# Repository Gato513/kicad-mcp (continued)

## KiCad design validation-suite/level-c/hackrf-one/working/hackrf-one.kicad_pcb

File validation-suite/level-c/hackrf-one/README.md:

# HackRF One (Great Scott Gadgets) — Validation Suite, Nivel C-01

Primera y ancla del Nivel C (complejidad alta / frontera refutatoria) del
flujo canónico de `kicad-mcp` (sesión 33, Fase 4, D-30.1/D-30.4). Tercer y
último punto de evidencia sobre los umbrales D-30.3 — cierra la trilogía
A ([anavi-dev-mic](../../level-a/anavi-dev-mic/)) + B
([anavi-macro-pad-12](../../level-b/anavi-macro-pad-12/)) + C. Hereda el
template metodológico establecido por Nivel A/B.

## Origen

- **Upstream**: https://github.com/greatscottgadgets/hackrf
  (`hardware/hackrf-one/`).
- **Commit canónico**: `24b53345afb79ebe34129bb68396614ab75f5637`
  ("HackRF One: update version to 10"), branch `main`.
- **Licencia**: **CERN-OHL-P v2** (permisiva) — verificado localmente
  contra el archivo `LICENSE` del propio directorio. **Corrige una
  premisa del prompt de sesión**, que citaba GPL-2/CC-BY (esa combinación
  aplica al firmware/software del proyecto HackRF más amplio, no al
  hardware de `hackrf-one/`, que tiene su propio `LICENSE`).
- **Descripción**: SDR (software-defined radio) de 1 MHz a 6 GHz, USB 2.0,
  MCU + CPLD + frontend RF, 4 capas.

## Admisión (6 criterios, D-33.1 — cada uno con su refutación explícita)

1. **PCB fabricada**: ✅ producto comercial en venta activa por Great Scott
   Gadgets (referencia industrial, featured en KiCad.org "Made with
   KiCad"). Refutación buscada: ¿evidencia más allá del propio repo? Sí —
   es hardware ampliamente distribuido y clonado (7.9k★/1.7k forks),
   citado en publicaciones de seguridad/RF.
2. **Proyecto mantenido**: ⚠️ **matiz, no refutación limpia**. Verificado
   localmente (`git log -- hardware/hackrf-one/`): último commit
   **2023-12-11** (`24b53345`, "update version to 10"), no 2024-02-07 como
   había estimado una verificación remota previa (LLM) — **corrección
   D-33.1**: la fecha remota inicial era incorrecta, la real es aún más
   vieja (~2 años 8 meses al momento de sesión 33). Dispara el trigger de
   ">2 años sin commits sobre hardware" del prompt. **Decisión del
   arquitecto (`AskUserQuestion`, pre-Bloque 0): admitir de todas formas**
   — producto en venta activa, hardware r10 estable, sin necesidad de
   revisión de layout desde entonces. Existe rama `h1r9` (revisión r9) no
   evaluada — fuera de alcance, `main` es la referencia.
3. **Buenas prácticas de KiCad**: ✅ revisión OK — stackup RF documentado
   explícitamente en el `.kicad_pcb` (dieléctricos con espesor real),
   netclasses declaradas (`Default` únicamente — ver "Hallazgo
   estructural" abajo), símbolo custom (`74AUP2G58GU.kicad_sym`) con
   `sym-lib-table`/`fp-lib-table` propios.
4. **Licencia compatible**: ✅ CERN-OHL-P v2 (permisiva) — mejor que lo
   estimado en el prompt.
5. **Esquemático + PCB completos**: ✅, con matiz — **`.kicad_sch` es
   MULTI-HOJA** (`grep -c "(sheet " hackrf-one.kicad_sch` = 3: `baseband`,
   `frontend`, `mcu`). Primera entrada jerárquica de la Suite. **No
   bloquea**: verificado que ni `run_erc()` ni
   `get_world_context(kind="sch")` se usan en el flujo canónico de Nivel
   A/B (grep sobre ambos `validation-report.md`, cero hits) — el flujo va
   por `route_board`/`fill_zones`/etc. contra el **board vivo**
   (`kind="pcb"`), que no tiene noción de jerarquía de esquemático.
6. **DRC 0/0 en el ground truth**: ❌ **NO cumple** — 470 violaciones
   totales en el original (22 `error`, 448 `warning` según el campo
   `severity` del JSON de `kicad-cli`; 0 `unconnected_items`). **Mismo
   precedente sancionado
   que Nivel A/B** (excepción documentada): el desglose (`text_height`
   ×199, `lib_footprint_mismatch` ×199, `lib_footprint_issues` ×23,
   `starved_thermal` ×13, `text_thickness` ×13, `silk_edge_clearance`
   ×13, `footprint_type_mismatch` ×7, `padstack` ×2,
   `nonmirrored_text_on_back_layer` ×1) es mayoritariamente cosmético o
   producto de no tener localmente las librerías custom exactas del
   autor (`lib_footprint_mismatch`/`lib_footprint_issues`, 222/470 = 47%)
   — mismo patrón ya visto en ambos niveles previos. **0 `unconnected_items`
   confirma que el ground truth está 100% ruteado** (no hay indicio de
   que el autor haya dejado nets sin conectar).

## Diversidad D-30.4 (features nuevas de Nivel C)

Contra `validation-suite/reports/coverage-matrix.md` (estado post Nivel B):

- **4 capas de cobre reales** (`F.Cu`≡`C1F`, `In1.Cu`≡`C2`, `In2.Cu`≡`C3`,
  `B.Cu`≡`C4B` — nombres de capa custom del autor, no los canónicos de
  KiCad) — primera entrada de la Suite. **Nota importante para Bloque
  2/3**: en el ground truth, las capas internas concentran la MAYORÍA del
  cobre (`C2` 8182mm², `C3` 7767mm² — más que `C1F`/`C4B` juntas) pero
  casi ningún track de señal (`C2` 29 segmentos, `C3` 15 segmentos, vs.
  `C1F` 2848 y `C4B` 925) — el ground truth mismo usa las capas internas
  casi exclusivamente como **planos**, no para rutear señal. Esto
  recalibra la expectativa de H1b: "0 tracks de señal en capas internas"
  en el output NO sería necesariamente una refutación si el ground truth
  tampoco los tiene.
- **Stackup RF real** con espesores de dieléctrico declarados (prepreg
  0.2104mm ×2, core 1.065mm — total 1.6116mm) — primera vez que la Suite
  ejercita un `.kicad_pcb` con `(stackup ...)` no trivial.
- **Escala**: 437 footprints / 380 nets / 3817 segmentos / 498 vías — ~8×
  Nivel B en nets (48), ~7× en footprints (63). Salto de escala, no
  incremental.
- **Esquemático jerárquico multi-hoja** (3 sub-hojas) — primera vez.
- **Footprints QFN/alta densidad** — MCU (LPC4320) y CPLD en QFN,
  densidad global del ground truth 90.17% (capa `C2`, la de mayor
  cobre) — más denso que Nivel B (63.88% B.Cu).
- **RF**: conectores SMA, antena, frontend de RF con componentes pasivos
  de precisión — régimen no ejercitado por A/B.
- **USB 2.0** (conector propio en el board, a diferencia de A/B donde el
  USB vivía dentro de un módulo XIAO externo) — primera vez con cobre de
  USB propio en la Suite.

**No confirmado como diversidad — refutado antes de ejecutar (D-33.1)**:
netclasses de impedancia. Ver "Hallazgo estructural" abajo.

## Hallazgo estructural (refutación D-33.1, previa a cualquier ejecución)

Verificado localmente contra `hackrf-one.kicad_pro` (`net_settings.classes`):
el ground truth define **una única netclass `Default`**
(track 0.127mm, clearance 0.127mm, vía 0.4572/0.254mm, con
`diff_pair_width`/`diff_pair_gap` poblados pero **sin ninguna asignación
de net** a clases distintas de `Default`). Mismo patrón que **todos** los
proyectos ANAVI verificados en Nivel A/B (BACKLOG P2, "ningún proyecto del
catálogo ANAVI asigna netclasses en la práctica").

⇒ **La sub-hipótesis de H1b "netclasses respetadas" queda refutada por el
propio ground truth, antes de tocar `route_board`.** No es un hallazgo
nuevo sobre el código (ya documentado en BACKLOG P2 desde sesión 32,
"candidato a Nivel C/D si aparece un board con asignación real") — HackRF
One tampoco la ejercita. El control de impedancia de este board es
**geométrico** (anchos de trace dibujados a mano por el autor sobre pistas
específicas, visible en el `.kicad_pcb` como tracks con `width` explícito
distinto del netclass default), no por reglas de netclass — evidencia
directa de que el control de impedancia RF real no pasa por el mecanismo
que `route_board`/`rules_reader.py` ignora. H1b sesión 33 queda acotada a:
uso de capas internas, densidad/escala, USB (conector propio, sin
diff-pair dirigido — ver arriba).

## Migración de formato (primera migración de un sch JERÁRQUICO de la Suite)

- **Original**: `(kicad_pcb (version 20211014) (generator pcbnew))` /
  `(kicad_sch (version 20211123) (generator eeschema))` en las 4 hojas —
  formato nativo de KiCad 6 (2021). Mismas versiones exactas que Nivel B.
- **Procedimiento**: `kicad-cli sch upgrade --force` sobre la hoja raíz
  **no migra las sub-hojas automáticamente** — hallazgo de esta sesión,
  no documentado en el precedente de Nivel B (single-sheet). Se migró
  cada una de las 3 sub-hojas (`baseband.kicad_sch`, `frontend.kicad_sch`,
  `mcu.kicad_sch`) individualmente con el mismo comando, además de
  `kicad-cli pcb upgrade --force` sobre el `.kicad_pcb`.
- **Migrado**: `(version 20260306)` (sch, las 4 hojas) / `(version
  20260206)` (pcb).
- **DRC pre vs. post migración**:

  | | Total | Errores | Warnings | Unconnected |
  |---|---|---|---|---|
  | Original (pre) | 470 | 22 | 448 | 0 |
  | Migrado (post) | 447 | 22 | 425 | 0 |

  Los 22 errores son **idénticos** pre/post (mismo conteo exacto),
  desglosados en `starved_thermal` (13), `footprint_type_mismatch` (7),
  `padstack` (2) — ninguno es `clearance`/`shorting_items`/
  `hole_clearance`/`courtyards_overlap` (las categorías eléctricas/
  estructurales graves de D-32.1); son defectos preexistentes del layout
  del autor, no bugs de conectividad. El descenso de warnings (448→425)
  es enteramente explicado por una **re-etiquetación de reglas** de
  kicad-cli, no por una corrección real:
  `lib_footprint_mismatch` (199 pre) → 0 post, `lib_footprint_issues` (23
  pre) → 199 post (la diferencia neta, -23, es la única variación real;
  todo lo demás —`text_height`, `text_thickness`, `starved_thermal`,
  `silk_edge_clearance`, `footprint_type_mismatch`, `padstack`,
  `nonmirrored_text_on_back_layer`— idéntico pre/post, conteo por conteo).
- **Chequeo de trivialidad (D-33.1 — refutar activamente antes de
  aceptar)**: comparación estructural pre/post vía `pcbnew` directo
  (segmentos, arcos, vías, zonas, keepouts, footprints, nets) — **los 7
  conteos son IDÉNTICOS bit a bit** (3817 segmentos, 0 arcos, 498 vías, 6
  zonas, 3 keepouts, 437 footprints, 380 nets, ambos lados). La migración
  es geométricamente un no-op; el único cambio real es el re-etiquetado
  de 23 violaciones DRC entre dos categorías de librería. **Hipótesis
  "migración trivial" sobrevive el intento de refutación** — se acepta.

## Estado de `working/`

Preparado con `prepare_working.py` sin modificaciones (reutilizado sin
cambios de Nivel A/B): 437 footprints en `(0,0)`, 0 tracks, 0 vías, 0
zonas, 32 dibujos en Edge.Cuts conservados. Verificado con asserts del
propio script (no en silencio).

## Métricas de referencia del ground truth (`gt-measured.json`, schema 1.2)

| Métrica | Valor |
|---|---|
| DRC | 22 errores / 425 warnings (447 total, 0 unconnected) |
| Longitud total de tracks | 9046.949 mm |
| Vías | 498 (100% `through` — sin blind/buried pese a 4 capas) |
| Cobre (unión) | 20345.17 mm² |
| Cobre por capa | C1F 2519.54 · C2 8182.34 · C3 7766.57 · C4B 1876.73 mm² |
| Footprints / Nets | 437 / 380 |
| Densidad (capa máxima / área board) | 90.17% |
| Área del board | 9074.44 mm² |

`drc_errors`/`drc_warnings` del script (22/425) coinciden exactamente con
el campo `severity` crudo de `kicad-cli` post-migración (22 `error` / 425
`warning`) — sin reclasificación, la fusión `violations`+
`unconnected_items` de `_run_drc` es aditiva únicamente.

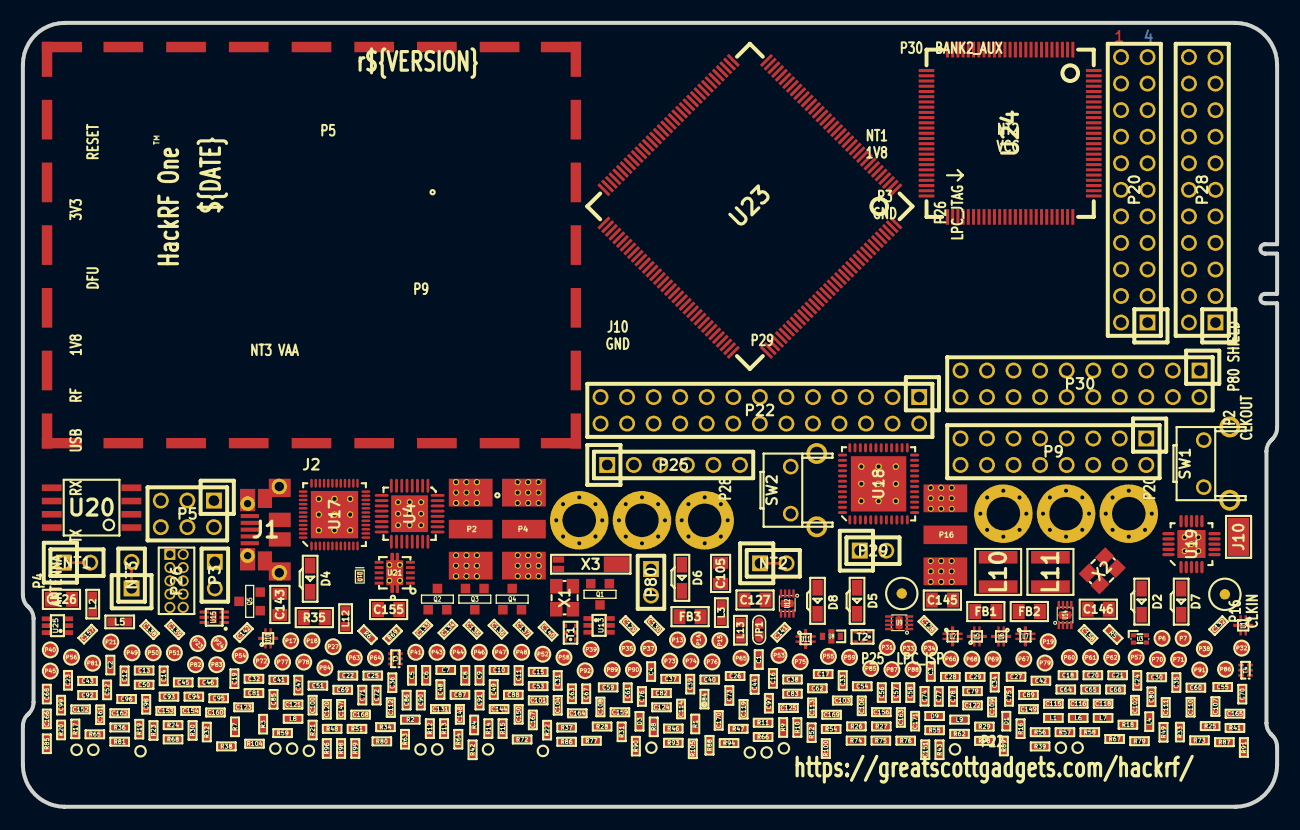
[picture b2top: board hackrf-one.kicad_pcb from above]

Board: 4 copper layers, 120.0 x 75.0 mm, 437 parts (0 on the bottom side), 319 nets, no tracks yet.

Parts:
C1, C3, C5, C7, C11, C24, C29, C33, C34, C35, C36, C37, C38, C39, C40, C45, C47, C55, C57, C60, C63, C65, C66, C67, C115, C125: 33pF; GSG-0402
C2, C4, C6, C10, C16, C19, C22, C30, C54, C56, C87, C88, C89, C92, C93, C162, C163: 10nF; GSG-0402
C8, C21, C32, C43, C48, C51, C84, C85, C86, C94, C95, C96, C99, C101, C102, C103, C107, C108, C109, C110: 22pF; GSG-0402
C9, C17, C18, C20, C23, C25, C28, C31, C44, C46, C49, C50, C58, C59, C61, C62, C64, C71, C73, C75, C77, C79, C81, C83, C91, C113, C119, C120, C121, C122, C123, C128, C129, C130, C131, C132, C133, C134, C135, C136, C137, C138, C139, C140, C141, C142, C144, C147, C148, C149, C150, C151, C152, C153, C154, C166, C167: 100nF; GSG-0402
C12, C13: 330pF; GSG-0402
C14: 8p2; GSG-0402
C15, C112: 180pF; GSG-0402
C26, C27, C116, C156: 47pF; GSG-0402
C41, C42, C52, C68, C69, C70, C90, C159, C160, C165, C168: 100pF; GSG-0402
C53, C106, C161, C171: 1uF; GSG-0402
C72, C74, C76, C78, C80, C82, C124: 2.2uF; GSG-0402
C97, C98, C100: 330nF; GSG-0402
C104, C111: 3pF; GSG-0402
C105, C126, C127, C143, C145, C146: 10uF; GSG-0805
C114: 3.3nF; GSG-0402
C118, C157, C158, C164: 18pF; GSG-0402
C155: DNP; GSG-0805
C169, C170: 1.8pF; GSG-0402
D1, D3, D9: GSG-DIODE-TVS-BI; GSG-0402
D2: VAALED; LTST-S220
D4: USBLED; LTST-S220
D5: RXLED; LTST-S220
D6: TXLED; LTST-S220
D7: VCCLED; LTST-S220
D8: 1V8LED; LTST-S220
D10: D_Schottky; DSN1006-2
FB1, FB2, FB3: FILTER; GSG-0805
FID1, FID2: FIDUCIAL; GSG-MARK1MM
J1: USB-MICRO-B; GSG-USB-MICROB-FCI-10103592-EXT
J2: RF-SHIELD-FRAME; GSG-SHIELD-BMI-S-230
J4, J5, J6, J7, J8, J9: MOUNTING_HOLE; GSG-HOLE126MIL-COPPER
J10: GND_CLIP; GSG-TEST-POINT-S1751-46R
JP1: Jumper; 0603-JUMPER
L1, L4, L6, L8, L9: DNP; GSG-0402
L2, L3, L5, L12, L13: 10uH; GSG-0603
L7: 6.2nH; GSG-0402
L10, L11: 4u7; GSG-NRG4026
NT1: 1V8; HEADER-1x2-SHORTED
NT2: VCC; HEADER-1x2-SHORTED
NT3: VAA; HEADER-1x2-SHORTED
P2: CLKOUT; GSG-SMA-73251-2120
P3: GND; GSG-HEADER-NOMARK-1x2
P4: ANTENNA; GSG-SMA-73251-2120
P5: LEDS; GSG-HEADER-2x3
P6: GPO4; GSG-TESTPOINT-50MIL
P7: GPO2; GSG-TESTPOINT-50MIL
P9: BASEBAND; GSG-HEADER-2x8
P13: GPO1; GSG-TESTPOINT-50MIL
P14: XCVR_CLKOUT; GSG-TESTPOINT-50MIL
P15: INTR; GSG-TESTPOINT-50MIL
P16: CLKIN; GSG-SMA-73251-2120
P17: GPO6; GSG-TESTPOINT-50MIL
P18: OEB; GSG-TESTPOINT-50MIL
P19: GPO3; GSG-TESTPOINT-50MIL
P20: GPIO; GSG-HEADER-2x11
P21: REF_IN; GSG-TESTPOINT-50MIL
P22: I2S; GSG-HEADER-2x13
P23: DBGEN; GSG-TESTPOINT-50MIL
P24: TRST; GSG-TESTPOINT-50MIL
P25: LPC_ISP; GSG-HEADER-1x6
P26: LPC_JTAG; GSG-50MIL-HEADER-2x5-TH
P27: MIXER_SDATA; GSG-TESTPOINT-50MIL
P28: SD; GSG-HEADER-2x11
P29: CPLD_JTAG; GSG-HEADER-1x2
P30: BANK2_AUX; GSG-HEADER-2x10
P31: MIXER_SCLK; GSG-TESTPOINT-50MIL
P32: MIXER_ENX; GSG-TESTPOINT-50MIL
P33: MIXER_RESETX; GSG-TESTPOINT-50MIL
P34: MIX_BYPASS; GSG-TESTPOINT-50MIL
P35: !MIX_BYPASS; GSG-TESTPOINT-50MIL
P37: SCL; GSG-TESTPOINT-50MIL
P38: SDA; GSG-TESTPOINT-50MIL
P39: SSP1_SCK; GSG-TESTPOINT-50MIL
P40: SSP1_COPI; GSG-TESTPOINT-50MIL
P41: SSP1_CIPO; GSG-TESTPOINT-50MIL
P43: RX; GSG-TESTPOINT-50MIL
P44: HP; GSG-TESTPOINT-50MIL
P45: LP; GSG-TESTPOINT-50MIL
P46: TX_MIX_BP; GSG-TESTPOINT-50MIL
P47: RX_MIX_BP; GSG-TESTPOINT-50MIL
P48: TX_AMP; GSG-TESTPOINT-50MIL
P49: RX_AMP; GSG-TESTPOINT-50MIL
P50: AMP_BYPASS; GSG-TESTPOINT-50MIL
P51: !TX_AMP_PWR; GSG-TESTPOINT-50MIL
P52: !RX_AMP_PWR; GSG-TESTPOINT-50MIL
P53: CS_XCVR; GSG-TESTPOINT-50MIL
P54: CS_AD; GSG-TESTPOINT-50MIL
P55: TXENABLE; GSG-TESTPOINT-50MIL
P56: RXENABLE; GSG-TESTPOINT-50MIL
P57: XTAL2; GSG-TESTPOINT-50MIL
P58: GCK1; GSG-TESTPOINT-50MIL
P59: GCK2; GSG-TESTPOINT-50MIL
P60: SGPIO_CLK; GSG-TESTPOINT-50MIL
P61: DA0; GSG-TESTPOINT-50MIL
P62: DA7; GSG-TESTPOINT-50MIL
P63: DD0; GSG-TESTPOINT-50MIL
P64: DD9; GSG-TESTPOINT-50MIL
P65: DA4; GSG-TESTPOINT-50MIL
P66: DD5; GSG-TESTPOINT-50MIL
P67: RSSI; GSG-TESTPOINT-50MIL
P68: SPIFI_CS; GSG-TESTPOINT-50MIL
P69: VREGMODE; GSG-TESTPOINT-50MIL
P70: EN_1V8; GSG-TESTPOINT-50MIL
P71: ID; GSG-TESTPOINT-50MIL
P72: GP_CLKIN; GSG-TESTPOINT-50MIL
P73: P1_2; GSG-TESTPOINT-50MIL
P74: P1_1; GSG-TESTPOINT-50MIL
P75: SGPIO0; GSG-TESTPOINT-50MIL
P76: SGPIO7; GSG-TESTPOINT-50MIL
P77: SGPIO9; GSG-TESTPOINT-50MIL
P78: SGPIO10; GSG-TESTPOINT-50MIL
P79: SGPIO11; GSG-TESTPOINT-50MIL
P80: SHIELD; GSG-HEADER-NOMARK-1x2
P81: SPIFI_SIO2; GSG-TESTPOINT-50MIL
P82: SPIFI_SIO3; GSG-TESTPOINT-50MIL
P83, P84, P85, P86, P87, P88, P89, P90, P91, P92: GND; GSG-TESTPOINT-50MIL
Q1, Q2, Q3, Q4, Q5: MOSFET_P; SOT23-3
R1, R2, R72, R75: 470; GSG-0402
R3: 22k; GSG-0402
R4: 51k; GSG-0402
R5, R6, R7, R11, R12, R24, R29, R36, R37, R41, R48, R49, R51, R52, R54, R59, R62, R63, R64, R66, R67, R68, R85, R93, R104, R105: 10k; GSG-0402
R8, R9, R10, R13, R73, R76: 1k; GSG-0402
R14, R15, R16, R17: 4k7; GSG-0402
R18, R27, R28, R74: 1k8; GSG-0402
R19, R30, R31, R32, R33, R34, R77, R78, R79, R80, R81, R86, R87, R88, R89, R90, R91, R94, R96, R98, R99, R100: 39; GSG-0402
R20, R21, R22, R23, R57, R58: 0; GSG-0402
R25, R26: 475; GSG-0402
R35: DNP; GSG-0805
R38: 15.4k; GSG-0402
R39, R47: 330k; GSG-0402
R42, R43: 18; GSG-0402
R46, R55: 162k; GSG-0402
R56: 715k; GSG-0402
R65: 18k; GSG-0402
R69: 12k; GSG-0402
SW1: DFU; GSG-SWITCH-FSMRA
SW2: RESET; GSG-SWITCH-FSMRA
T1: MIX_IN_BALUN; GSG-B0310J50100AHF
T2: MIX_OUT_BALUN; GSG-B0310J50100AHF
T3: RX_BALUN; GSG-2500BL14M100
T4: TX_BALUN; GSG-2500BL14M100
TESTPOINT-30MIL-MASKONLY: VAL**; GSG-TESTPOINT-30MIL-MASKONLY
TP1, TP2, TP3, TP4, TP5, TP6, TP7, TP8, TP9, TP10, TP11, TP12, TP13, TP14, TP15, TP16: VAL**; GSG-TESTPOINT-30MIL-MASKONLY
U1, U2, U5, U6, U7, U10, U11: SKY13453; SKY13350-385LF
U3: LOWPASS_FILTER; GSG-LP0603
U4: RFFC5072; GSG-QFN32
U8: HIGHPASS_FILTER; GSG-HP-DEA
U9, U12, U14: SKY13317; GSG-SKY13317-373LF
U13, U25: MGA-81563; GSG-SOT363
U15: TVS; GSG-LXES1TBCC2-004
U17: MAX2837; GSG-QFN48-6
U18: MAX5864; GSG-QFN48-7
U19: SI5351C; GSG-QFN20-4
U20: W25Q80; GSG-SOIC8-208
U21: TPS62410; GSG-S-PVSON-N10
U23: LPC4320FBD144; GSG-LQFP144
U24: GSG-XC2C64A-7VQG100C; GSG-VQ100
X1: MAIN_XTAL; GSG-XTAL3.2x2.5mm
X2: MCU_XTAL; GSG-XTAL3.2x2.5mm
X3: RTC_XTAL; GSG-XTAL-AB26TRQ

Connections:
!MIX_BYPASS: C7.2, C38.2, P35.1, U1.5 (VCTL), U9.6 (V2), U23.50 (P1_7)
!RX_AMP_PWR: P52.1, Q1.1 (G), R29.2, U23.106 (P2_12)
!TX_AMP_PWR: P51.1, Q2.1 (G), R24.1, U23.97 (P6_9)
!VAA_ENABLE: P5.5, Q3.1 (G), R11.2, U23.37 (P5_0)
+1V8: C151.1, C152.1, NT1.1, U24.26 (VCC), U24.57 (VCC)
/baseband/CLK0: R31.2, U19.13 (CLK0)
/baseband/CLK1: R32.2, U19.12 (CLK1)
/baseband/CLK2: R94.2, U19.9 (CLK2)
/baseband/CLK3: R33.2, U19.8 (CLK3)
/baseband/CLK5: C115.1, U19.17 (CLK5)
/baseband/COM: C97.1, U18.47 (COM)
/baseband/CPOUT+: C112.2, R25.1, U17.23 (CPOUT+)
/baseband/CPOUT-: C112.1, R26.1, U17.24 (CPOUT-)
/baseband/IA+: C101.1, C110.1, R20.1, U18.3 (IA+)
/baseband/IA-: C101.2, C109.1, R21.1, U18.4 (IA-)
/baseband/ID+: R13.1, U18.45 (ID+)
/baseband/ID-: R10.1, U18.44 (ID-)
/baseband/INTR: P15.1, R104.2, U19.3 (INTR)
/baseband/OEB: P18.1, R105.2, U19.7 (OEB)
/baseband/QA+: C103.2, C107.1, R23.1, U18.10 (QA+)
/baseband/QA-: C103.1, C108.1, R22.1, U18.9 (QA-)
/baseband/QD+: R8.1, U18.40 (QD+)
/baseband/QD-: R9.1, U18.41 (QD-)
/baseband/REFN: C98.1, U18.48 (REFN)
/baseband/REFP: C100.1, U18.1 (REFP)
/baseband/RXBBI+: P9.7, R20.2, U17.38 (RXBBI+)
/baseband/RXBBI-: P9.5, R21.2, U17.37 (RXBBI-)
/baseband/RXBBQ+: P9.6, R22.2, U17.36 (RXBBQ+)
/baseband/RXBBQ-: P9.4, R23.2, U17.35 (RXBBQ-)
/baseband/TXBBI+: C96.1, P9.12, R10.2, R15.1, U17.43 (TXBBI+)
/baseband/TXBBI-: C96.2, P9.10, R13.2, R14.1, U17.42 (TXBBI-)
/baseband/TXBBQ+: C95.2, P9.11, R9.2, R16.1, U17.44 (TXBBQ+)
/baseband/TXBBQ-: C95.1, P9.13, R8.2, R17.1, U17.45 (TXBBQ-)
/baseband/XA: C170.2, U19.1 (XA), X1.3
/baseband/XB: C169.2, U19.2 (XB), X1.1
/baseband/XCVR_CLKOUT: P14.1, U17.16 (CLOCKOUT)
/baseband/XTAL2: C115.2, C116.1, P57.1, U17.17 (XTAL2)
/frontend/!ANT_BIAS: P13.1, Q4.1 (G), R36.1, U4.15 (GPO1/ADD1)
/frontend/REF_IN: C67.2, C70.1, P21.1, U4.10 (REF_IN)
/frontend/RX_AMP_IN: C58.1, U14.8 (RF3)
/frontend/RX_AMP_OUT: C50.2, U12.4 (RF1)
/frontend/TX_AMP_IN: C59.1, U12.8 (RF3)
/frontend/TX_AMP_OUT: C62.1, U14.4 (RF1)
/mcu/usb/power/ADC0_0: P20.20, U23.6 (ADC0_0/ADC1_0/DAC)
/mcu/usb/power/ADC0_2: P20.16, U23.143 (ADC0_2/ADC1_2)
/mcu/usb/power/ADC0_3: R38.2, R39.1, U23.139 (ADC0_3/ADC1_3)
/mcu/usb/power/ADC0_5: P20.18, U23.144 (ADC0_5/ADC1_5)
/mcu/usb/power/ADC0_6: P20.14, U23.142 (ADC0_6/ADC1_6)
/mcu/usb/power/B1AUX13: P28.16, U24.55 (BANK1F4M13)
/mcu/usb/power/B1AUX14: P28.15, U24.56 (BANK1F4M14)
/mcu/usb/power/B2AUX1: P30.18, U24.13 (BANK2F1M1)
/mcu/usb/power/B2AUX2: P30.17, U24.12 (BANK2F1M2)
/mcu/usb/power/B2AUX3: P30.16, U24.11 (BANK2F1M3)
/mcu/usb/power/B2AUX4: P30.15, U24.10 (BANK2F1M4)
/mcu/usb/power/B2AUX5: P30.14, U24.9 (BANK2F1M5)
/mcu/usb/power/B2AUX6: P30.13, U24.8 (BANK2F1M6)
/mcu/usb/power/B2AUX7: P30.12, U24.7 (BANK2F1M7)
/mcu/usb/power/B2AUX8: P30.11, U24.6 (BANK2F1M8)
/mcu/usb/power/B2AUX9: P30.10, U24.4 (BANK2F1M9)
/mcu/usb/power/B2AUX10: P30.9, U24.3 (BANK2F1M10)
/mcu/usb/power/B2AUX11: P30.8, U24.2 (BANK2F1M11)
/mcu/usb/power/B2AUX12: P30.7, U24.1 (BANK2F1M12)
/mcu/usb/power/B2AUX13: P30.6, U24.99 (BANK2F1M13)
/mcu/usb/power/B2AUX14: P30.5, U24.97 (BANK2F1M14)
/mcu/usb/power/B2AUX15: P30.4, U24.94 (BANK2F1M15)
/mcu/usb/power/B2AUX16: P30.3, U24.92 (BANK2F1M16)
/mcu/usb/power/BANK2F3M1: R77.2, U24.91 (BANK2F3M1)
/mcu/usb/power/BANK2F3M2: P28.18, R78.2, U24.90 (BANK2F3M2)
/mcu/usb/power/BANK2F3M3: R79.2, U24.89 (BANK2F3M3)
/mcu/usb/power/BANK2F3M4: P28.22, R80.2, U24.81 (BANK2F3M4)
/mcu/usb/power/BANK2F3M5: R81.2, U24.79 (BANK2F3M5)
/mcu/usb/power/BANK2F3M6: P28.20, R86.2, U24.78 (BANK2F3M6)
/mcu/usb/power/BANK2F3M7: R87.2, U24.77 (BANK2F3M7)
/mcu/usb/power/BANK2F3M8: R88.2, U24.76 (BANK2F3M8)
/mcu/usb/power/BANK2F3M9: R89.2, U24.74 (BANK2F3M9)
/mcu/usb/power/BANK2F3M10: R90.2, U24.72 (BANK2F3M10)
/mcu/usb/power/BANK2F3M11: R91.2, U24.71 (BANK2F3M11)
/mcu/usb/power/BANK2F3M12: P28.21, R96.2, U24.70 (BANK2F3M12)
/mcu/usb/power/BANK2F3M14: R98.2, U24.67 (BANK2F3M14)
/mcu/usb/power/BANK2F3M15: R99.2, U24.64 (BANK2F3M15)
/mcu/usb/power/BANK2F3M16: R100.2, U24.61 (BANK2F3M16)
/mcu/usb/power/CPLD_TCK: P28.17, U23.74 (P6_1), U24.48 (TCK)
/mcu/usb/power/CPLD_TDI: P28.19, U23.78 (P6_2), U24.45 (TDI)
/mcu/usb/power/CPLD_TDO: P29.2, U23.69 (P9_5), U24.83 (TDO)
/mcu/usb/power/CPLD_TMS: P29.1, U23.82 (P6_5), U24.47 (TMS)
/mcu/usb/power/DBGEN: P23.1, R64.1, U23.28 (DBGEN)
/mcu/usb/power/DM: R58.1, U23.20 (USB0_DM)
/mcu/usb/power/DP: R57.1, U23.18 (USB0_DP)
/mcu/usb/power/EN1V8: P70.1, R54.2, R76.2, U21.9 (EN2), U23.100 (P6_10)
/mcu/usb/power/GCK0: P30.19, U24.22 (BANK1F2M7)
/mcu/usb/power/GPIO3_8: P20.5, U23.110 (P7_0)
/mcu/usb/power/GPIO3_9: P20.6, U23.113 (P7_1)
/mcu/usb/power/GPIO3_10: P20.7, U23.115 (P7_2)
/mcu/usb/power/GPIO3_11: P20.8, U23.117 (P7_3)
/mcu/usb/power/GPIO3_12: P20.9, U23.132 (P7_4)
/mcu/usb/power/GPIO3_13: P20.10, U23.133 (P7_5)
/mcu/usb/power/GPIO3_14: P20.11, U23.134 (P7_6)
/mcu/usb/power/GPIO3_15: P20.12, U23.140 (P7_7)
/mcu/usb/power/GP_CLKIN: C156.1, P72.1, R34.1, U23.14 (P4_7)
/mcu/usb/power/I2C1_SCL: P22.5, U23.88 (P2_4)
/mcu/usb/power/I2C1_SDA: P22.6, U23.87 (P2_3)
/mcu/usb/power/I2S0_RX_MCLK: P22.14, U23.73 (P6_0)
/mcu/usb/power/I2S0_RX_SCK: P22.12, U23.120 (PF_4)
/mcu/usb/power/I2S0_RX_SDA: P22.13, U23.116 (P3_2)
/mcu/usb/power/I2S0_RX_WS: P22.15, U23.114 (P3_1)
/mcu/usb/power/I2S0_TX_MCLK: P22.17, U23.99 (CLK2)
/mcu/usb/power/I2S0_TX_SCK: P22.16, U23.112 (P3_0)
/mcu/usb/power/ISP: P25.2, R59.2, U23.96 (P2_7)
/mcu/usb/power/LED1: P5.3, R72.2, U23.3 (P4_1)
/mcu/usb/power/LED2: P5.4, R73.2, U23.8 (P4_2)
/mcu/usb/power/LED3: P5.6, R74.2, U23.103 (P6_12)
/mcu/usb/power/P1_1: P74.1, R67.1, U23.42 (P1_1)
/mcu/usb/power/P1_2: P73.1, R68.1, U23.43 (P1_2)
/mcu/usb/power/P2_8: P22.23, R30.1, U23.98 (P2_8)
/mcu/usb/power/P2_9: P22.21, R93.1, U23.102 (P2_9)
/mcu/usb/power/P2_13: P22.22, U23.108 (P2_13)
/mcu/usb/power/REG_OUT1: C145.2, C146.2, L11.1, NT2.2, R56.1, U21.4 (FB1)
/mcu/usb/power/REG_OUT2: C125.1, C126.1, C127.1, L10.2, NT1.2, R47.1
/mcu/usb/power/RESET: P22.3, P25.6, P26.10, R19.1, U23.128 (RESET)
/mcu/usb/power/RREF: R69.1, U23.24 (USB0_RREF)
/mcu/usb/power/RTCX1: C118.1, U23.125 (RTCX1), X3.2
/mcu/usb/power/RTCX2: C164.1, U23.126 (RTCX2), X3.1
/mcu/usb/power/RTC_ALARM: P20.2, U23.129 (RTC_ALARM)
/mcu/usb/power/SD_CD: P28.3, U23.60 (P1_13)
/mcu/usb/power/SD_CLK: P28.11, U23.45 (CLK0)
/mcu/usb/power/SD_CMD: P28.9, U23.49 (P1_6)
/mcu/usb/power/SD_DAT0: P28.7, U23.52 (P1_9)
/mcu/usb/power/SD_DAT1: P28.6, U23.53 (P1_10)
/mcu/usb/power/SD_DAT2: P28.5, U23.55 (P1_11)
/mcu/usb/power/SD_DAT3: P28.4, U23.56 (P1_12)
/mcu/usb/power/SD_POW: P28.10, U23.48 (P1_5)
/mcu/usb/power/SD_VOLT0: P28.8, U23.51 (P1_8)
/mcu/usb/power/SGPIO0: P75.1, R79.1, U23.32 (P0_0)
/mcu/usb/power/SGPIO1: R81.1, U23.34 (P0_1)
/mcu/usb/power/SGPIO2: R89.1, U23.62 (P1_15)
/mcu/usb/power/SGPIO3: R90.1, U23.64 (P1_16)
/mcu/usb/power/SGPIO4: R98.1, U23.79 (P6_3)
/mcu/usb/power/SGPIO5: R99.1, U23.83 (P6_6)
/mcu/usb/power/SGPIO6: R100.1, U23.84 (P2_2)
/mcu/usb/power/SGPIO7: P76.1, R87.1, U23.38 (P1_0)
/mcu/usb/power/SGPIO9: P77.1, R77.1, U23.7 (P4_3)
/mcu/usb/power/SGPIO10: P78.1, R88.1, U23.61 (P1_14)
/mcu/usb/power/SGPIO11: P79.1, R91.1, U23.66 (P1_17)
/mcu/usb/power/SGPIO12: R96.1, U23.67 (P1_18)
/mcu/usb/power/SGPIO13: R78.1, U23.15 (P4_8)
/mcu/usb/power/SGPIO14: R80.1, U23.33 (P4_9)
/mcu/usb/power/SGPIO15: R86.1, U23.35 (P4_10)
/mcu/usb/power/SPIFI_CIPO: P22.7, U20.2 (DO), U23.122 (P3_6)
/mcu/usb/power/SPIFI_COPI: P22.9, U20.5 (DI), U23.123 (P3_7)
/mcu/usb/power/SPIFI_CS: P68.1, U20.1 (CS), U23.124 (P3_8)
/mcu/usb/power/SPIFI_SCK: P22.8, U20.6 (CLK), U23.118 (P3_3)
/mcu/usb/power/SPIFI_SIO2: P81.1, U20.3 (WP), U23.121 (P3_5)
/mcu/usb/power/SPIFI_SIO3: P82.1, U20.7 (HOLD), U23.119 (P3_4)
/mcu/usb/power/TCK: P26.4, R66.2, U23.27 (TCK/SWDCLK)
/mcu/usb/power/TDI: P26.8, U23.26 (TDI)
/mcu/usb/power/TDO: P26.6, R63.1, U23.31 (TDO/SWO)
/mcu/usb/power/TMS: P26.2, U23.30 (TMS/SWDIO)
/mcu/usb/power/U0_RXD: P22.19, P25.4, U23.81 (P2_1)
/mcu/usb/power/U0_TXD: P22.20, P25.5, U23.75 (P2_0)
/mcu/usb/power/USB_SHIELD: C155.1, J1.0 (SHIELD), P80.1, P80.2, R35.1
/mcu/usb/power/VBAT: C136.1, P20.1, U23.127 (VBAT)
/mcu/usb/power/VBUS: FB1.2, P20.21, Q5.2 (S), R62.2, U15.5 (VDD)
/mcu/usb/power/VBUSCTRL: P20.17, Q5.1 (G), R37.2
/mcu/usb/power/VIN: C143.1, C147.1, P20.22, Q5.3 (D), R52.1, U21.3 (VIN)
/mcu/usb/power/VREGMODE: P69.1, R51.2, U23.101 (P6_11)
/mcu/usb/power/WAKEUP: P20.4, R48.2, U23.130 (WAKEUP0)
/mcu/usb/power/XTAL1: C157.1, U23.12 (XTAL1), X2.1
/mcu/usb/power/XTAL2: C158.1, U23.13 (XTAL2), X2.3
AMP_BYPASS: C57.1, C65.2, P50.1, U12.6 (V2), U14.6 (V2), U23.104 (P2_10)
CLK6: P22.25, U19.16 (CLK6)
CLKIN: D3.2 (K), P16.1 (RF), P22.2, R85.1, U19.6 (CLKIN)
CLKOUT: C165.1, D9.2 (K), P2.1 (RF), P22.1, R33.1
CS_AD: P54.1, U18.36 (CS), U23.65 (P5_7)
CS_XCVR: P53.1, U17.30 (CS), U23.70 (P1_20)
DA0: P61.1, U18.13 (DA0), U24.43 (BANK1F4M8)
DA1: U18.14 (DA1), U24.42 (BANK1F4M7)
DA2: U18.15 (DA2), U24.41 (BANK1F4M6)
DA3: U18.16 (DA3), U24.40 (BANK1F4M5)
DA4: P65.1, U18.19 (DA4), U24.39 (BANK1F4M4)
DA5: U18.20 (DA5), U24.37 (BANK1F4M3)
DA6: U18.21 (DA6), U24.36 (BANK1F4M2)
DA7: P62.1, U18.22 (DA7), U24.35 (BANK1F4M1)
DD0: P63.1, U18.23 (DD0), U24.34 (BANK1F2M16)
DD1: U18.24 (DD1), U24.33 (BANK1F2M15)
DD2: U18.25 (DD2), U24.32 (BANK1F2M14)
DD3: U18.26 (DD3), U24.30 (BANK1F2M13)
DD4: U18.27 (DD4), U24.29 (BANK1F2M12)
DD5: P66.1, U18.28 (DD5), U24.28 (BANK1F2M11)
DD6: U18.29 (DD6), U24.24 (BANK1F2M9)
DD7: U18.30 (DD7), U24.19 (BANK1F2M6)
DD8: U18.31 (DD8), U24.18 (BANK1F2M5)
DD9: P64.1, U18.32 (DD9), U24.17 (BANK1F2M4)
GCK1: C68.1, P28.14, P58.1, R31.1, U18.6 (CLK), U24.23 (BANK1F2M8)
GCK2: C69.1, P28.13, P59.1, R32.1, U24.27 (BANK1F2M10)
GND: C1.2, C2.2, C3.2, C4.2, C5.2, C6.2, C7.1, C10.1, C11.1, C12.2, C13.2, C16.2, C19.1, C22.1, C24.1, C25.2, C29.2, C30.2, C33.2, C34.2, C35.2, C36.2, C37.2, C38.1, C39.1, C40.1, C41.2, C42.2, C45.1, C47.1, C49.1, C52.2, C53.2, C54.2, C55.2, C56.2, C57.2, C60.1, C63.2, C65.1, C66.1, C68.2, C69.2, C70.2, C71.2, C72.2, C73.2, C74.2, C75.2, C76.2, C77.2, C78.2, C79.2, C80.2, C81.2, C82.2, C83.2, C84.2, C85.2, C86.2, C87.2, C88.2, C89.2, C90.2, C91.2, C92.2, C93.2, C94.2, C97.2, C98.2, C100.2, C105.2, C106.2, C107.2, C108.2, C109.2, C110.2, C113.2, C116.2, C118.2, C119.2, C120.2, C121.2, C122.2, C123.2, C124.2, C126.2, C127.2, C128.2, C129.2, C130.2, C131.2, C132.2, C133.2, C134.2, C135.2, C136.2, C137.2, C138.2, C139.2, C140.2, C141.2, C142.2, C143.2, C144.2, C145.1, C146.1, C147.2, C148.2, C149.2, C150.2, C151.2, C152.2, C153.2, C154.2, C155.2, C156.2, C157.2, C158.2, C159.2, C160.2, C161.2, C162.1, C163.1, C164.2, C165.2, C166.2, C167.2, C168.2, C169.1, C170.1, C171.2, D1.1 (A), D2.1 (K), D3.1 (A), D4.1 (K), D5.1 (K), D6.1 (K), D7.1 (K), D8.1 (K), D9.1 (A), FB3.2, J2.0 (SHIELD), J4.1, J5.1, J6.1, J7.1, J8.1, J9.1, J10.1, P2.2 (GND), P3.1, P3.2, P4.2 (GND), P5.1, P9.1, P9.2, P9.3, P9.8, P9.9, P9.14, P9.15, P9.16, P16.2 (GND), P20.13, P20.15, P20.19, P22.4, P22.10, P22.18, P25.1, P26.3, P26.5, P26.9, P28.2, P28.12, P30.2, P30.20, P83.1, P84.1, P85.1, P86.1, P87.1, P88.1, P89.1, P90.1, P91.1, P92.1, R4.1, R7.2, R14.2, R15.2, R16.2, R17.2, R35.2, R37.1, R39.2, R41.1, R46.1, R54.1, R55.1, R65.1, R68.2, R69.2, R85.2, R93.2, SW1.0 (SHIELD), SW2.0 (SHIELD), SW2.1, T3.2 (PC), T3.5 (S2), T4.2 (PC), T4.5 (S2), U1.3 (GND), U2.3 (GND), U3.2 (GND), U3.3 (GND), U4.0 (EP), U4.12 (TM), U5.3 (GND), U6.3 (GND), U7.3 (GND), U8.2 (GND), U8.4 (GND), U9.0 (GND), U10.3 (GND), U11.3 (GND), U12.0 (GND), U13.1 (GND), U13.2 (GND), U13.4 (GND), U13.5 (GND), U14.0 (GND), U15.2 (GND), U17.0 (EP), U17.2 (GNDRXLNA), U17.22 (GNDCP), U17.26 (GNDVCO), U18.0 (EP), U18.5 (GND), U18.7 (GND), U18.12 (GND), U18.17 (OGND), U18.37 (GND), U18.42 (GND), U19.0 (GND), U20.4 (GND), U21.0 (PP), U21.8 (GND), U23.4 (VSSIO), U23.19 (USB0_VSSA_TERM), U23.23 (USB0_VSSA_REF), U23.40 (VSSIO), U23.76 (VSSIO), U23.109 (VSSIO), U23.135 (VSSA), U23.138 (ADC0_4/ADC1_4), U24.21 (GND), U24.31 (GND), U24.62 (GND), U24.69 (GND), U24.84 (GND), U24.100 (GND), U25.1 (GND), U25.2 (GND), U25.4 (GND), U25.5 (GND), X1.2, X1.4, X2.2, X2.4
HP: C11.2, P44.1, U6.5 (VCTL), U23.1 (P4_0)
LP: C29.1, P45.1, U5.5 (VCTL), U23.39 (P5_1)
MCU_CLK: R34.2, U19.15 (CLK7)
MIXER_ENX: C35.1, P32.1, R6.2, U4.30 (ENX), U23.57 (P5_4)
MIXER_RESETX: C34.1, P33.1, R5.2, U4.29 (RESETX), U23.58 (P5_5)
MIXER_SCLK: C36.1, P31.1, U4.31 (SCLK), U23.95 (P2_6)
MIXER_SDATA: C37.1, P27.1, U4.32 (SDATA), U23.80 (P6_4)
MIX_BYPASS: C47.2, P34.1, U11.5 (VCTL), U23.86 (P6_8)
MIX_CLK: C67.1, U19.19 (CLK4)
unnamed: C8.2, U1.6 (RFC)
unnamed: C9.1, U7.2 (RF1)
unnamed: C9.2, U2.2 (RF1)
unnamed: C12.1, R1.2, U4.8 (LFILT3)
unnamed: C13.1, R1.1, R2.2
unnamed: C14.1, C15.1, R2.1, U4.7 (LFITLT2)
unnamed: C14.2, R3.1, U4.6 (LFILT1)
unnamed: C15.2, R3.2
unnamed: C17.1, U3.4 (IN)
unnamed: C17.2, U6.4 (RF2)
unnamed: C18.1, U5.2 (RF1)
unnamed: C18.2, U3.1 (OUT)
unnamed: C20.1, U6.6 (RFC)
unnamed: C20.2, U2.6 (RFC)
unnamed: C21.1, U1.2 (RF1)
unnamed: C21.2, U7.4 (RF2)
unnamed: C23.1, U10.4 (RF2)
unnamed: C23.2, U2.4 (RF2)
unnamed: C25.1, T1.2 (S2)
unnamed: C26.1, U8.3 (OUT)
unnamed: C26.2, U5.4 (RF2)
unnamed: C27.1, U8.1 (IN)
unnamed: C27.2, U6.2 (RF1)
unnamed: C28.1, T1.1 (S1)
unnamed: C28.2, U7.6 (RFC)
unnamed: C31.1, U9.5 (RF2)
unnamed: C31.2, U5.6 (RFC)
unnamed: C32.1, U1.4 (RF2)
unnamed: C32.2, U9.4 (RF1)
unnamed: C43.1, U9.8 (RF3)
unnamed: C43.2, U11.2 (RF1)
unnamed: C44.1, U12.1 (RFC)
unnamed: C44.2, U9.1 (RFC)
unnamed: C46.1, U10.6 (RFC)
unnamed: C46.2, T2.1 (S1)
unnamed: C48.1, U11.6 (RFC)
unnamed: C49.2, T2.2 (S2)
unnamed: C50.1, L5.2, U13.6 (OUT)
unnamed: C51.1, U11.4 (RF2)
unnamed: C51.2, U10.2 (RF1)
unnamed: C58.2, U13.3 (IN)
unnamed: C59.2, U25.3 (IN)
unnamed: C61.1, U14.5 (RF2)
unnamed: C61.2, U12.5 (RF2)
unnamed: C62.2, L12.2, U25.6 (OUT)
unnamed: C64.1, U14.1 (RFC)
unnamed: C64.2, D1.2 (K), L13.2, P4.1 (RF)
unnamed: C99.1, L7.1, U17.4 (RXRF+)
unnamed: C99.2, L6.1, T3.4 (PR2)
unnamed: C102.1, L7.2, U17.5 (RXRF-)
unnamed: C102.2, L6.2, T3.3 (PR1)
unnamed: C104.1, L9.1, U17.10 (TXRF+)
unnamed: C104.2, L8.1, T4.4 (PR2)
unnamed: C105.1, FB2.2, NT3.2
unnamed: C106.1, U17.27 (BYPASS)
unnamed: C111.1, L9.2, U17.11 (TXRF-)
unnamed: C111.2, L8.2, T4.3 (PR1)
unnamed: C114.1, R26.2
unnamed: C114.2, R25.2
unnamed: C125.2, R46.2, R47.2, U21.1 (ADJ2)
unnamed: C160.1, C162.2, L12.1, R43.1
unnamed: C52.1, C163.2, L5.1, R42.2
unnamed: D2.2 (A), R18.1
unnamed: D4.2 (A), R72.1
unnamed: D5.2 (A), R73.1
unnamed: D6.2 (A), R74.1
unnamed: D7.2 (A), R75.1
unnamed: D8.2 (A), R76.1
unnamed: D10.1 (K), JP1.1 (A), L13.1
unnamed: D10.2 (A), JP1.2 (B), Q4.3 (D)
unnamed: FB1.1, J1.1 (VBUS)
unnamed: FB2.1, Q3.3 (D)
unnamed: FB3.1, J1.5 (GND)
unnamed: J1.2 (D-), R58.2, U15.3 (ESD2)
unnamed: J1.3 (D+), R57.2, U15.1 (ESD1)
unnamed: J1.4 (ID), P71.1, R12.2, U23.22 (USB0_ID)
unnamed: L1.1, T1.4 (PR2), U4.23 (MIX_IPP)
unnamed: L1.2, T1.3 (PR1), U4.24 (MIX_IPN)
unnamed: L2.1, L4.2, T2.4 (PR2), U4.27 (MIX_OPN)
unnamed: L3.1, L4.1, T2.3 (PR1), U4.28 (MIX_OPP)
unnamed: L10.1, U21.10 (SW2)
unnamed: L11.2, U21.6 (SW1)
unnamed: P6.1, U4.26 (GPO4/LD/DO)
unnamed: P7.1, U4.16 (GPO2/ADD2)
unnamed: P17.1, U4.9 (MODE/GPO6)
unnamed: P19.1, U4.25 (GPO3/FM)
unnamed: P24.1, U23.29 (TRST)
unnamed: Q1.3 (D), R42.1
unnamed: Q2.3 (D), R43.2
unnamed: R4.2, U4.4 (REXT)
unnamed: R19.2, R49.2, SW2.2
unnamed: R7.1, R30.2, SW1.2
unnamed: R51.1, U21.2 (MODE/DATA)
unnamed: R52.2, U21.7 (EN1)
unnamed: R55.2, R56.2, U21.5 (DEF1)
unnamed: R62.1, R65.2, U23.21 (USB0_VBUS)
RSSI: P67.1, U17.32 (RSSI), U23.2 (ADC0_1/ADC1_1)
RX: C24.2, C33.1, C45.2, P43.1, U2.5 (VCTL), U7.5 (VCTL), U10.5 (VCTL), U23.91 (P2_5)
RXENABLE: P56.1, U17.48 (RXENABLE), U23.10 (P4_5)
RX_AMP: C60.2, C66.2, P49.1, U12.3 (V1), U14.7 (V3), U23.105 (P2_11)
RX_IF: C48.2, T3.1 (S1)
RX_MIX_BP: C40.2, P47.1, U9.7 (V3), U23.54 (P5_3)
SCL: P22.26, P37.1, R28.2, U19.4 (SCL), U23.92 (I2C0_SCL)
SDA: P22.24, P38.1, R27.2, U19.5 (SDA), U23.93 (I2C0_SDA)
SGPIO_CLK: C159.1, P60.1, R94.1, U23.72 (P9_6)
SSP1_CIPO: C168.1, P41.1, U17.29 (DOUT), U23.44 (P1_3)
SSP1_COPI: P40.1, U17.31 (DIN), U18.34 (DIN), U23.47 (P1_4)
SSP1_SCK: P39.1, U17.15 (SCLK), U18.35 (SCLK), U23.68 (P1_19)
TXENABLE: P55.1, U17.47 (TXENABLE), U23.9 (P4_4)
TX_AMP: C55.1, C63.1, P48.1, U12.7 (V3), U14.3 (V1), U23.63 (P5_6)
TX_IF: C8.1, T4.1 (S1)
TX_MIX_BP: C39.2, P46.1, U9.3 (V1), U23.46 (P5_2)
VAA: C3.1, C4.1, C5.1, C6.1, C10.2, C16.1, C19.2, C22.2, C30.1, C41.1, C42.1, C53.1, C54.1, C56.1, C71.1, C72.1, C73.1, C74.1, C75.1, C76.1, C77.1, C78.1, C79.1, C80.1, C81.1, C82.1, C83.1, C84.1, C85.1, C86.1, C87.1, C89.1, C90.1, C91.1, C92.1, C93.1, C94.1, C161.1, C166.1, C171.1, L2.2, L3.2, NT3.1, Q1.2 (S), Q2.2 (S), Q4.2 (S), R18.2, R24.2, R29.1, R36.2, U1.1 (VDD), U2.1 (VDD), U4.5 (ANA_VDD1), U4.22 (ANA_VDD2), U5.1 (VDD), U6.1 (VDD), U7.1 (VDD), U10.1 (VDD), U11.1 (VDD), U17.1 (VCCRXLNA), U17.7 (VCCTXPAD), U17.13 (VCCTXMX), U17.19 (VCCXTAL), U17.21 (VCCCP), U17.28 (VCCVCO), U17.39 (VCCRXVGA), U17.41 (VCCRXFL), U17.46 (VCCRXMX), U18.2 (VDD), U18.8 (VDD), U18.11 (VDD), U18.33 (VDD), U18.39 (VDD), U18.43 (VDD), U18.46 (REFIN)
VCC: C1.1, C2.1, C88.1, C113.1, C119.1, C120.1, C121.1, C122.1, C123.1, C124.1, C128.1, C129.1, C130.1, C131.1, C132.1, C133.1, C134.1, C135.1, C137.1, C138.1, C139.1, C140.1, C141.1, C142.1, C144.1, C148.1, C149.1, C150.1, C153.1, C154.1, C167.1, NT2.1, P5.2, P20.3, P22.11, P26.1, P28.1, P30.1, Q3.2 (S), R5.1, R6.1, R11.1, R12.1, R27.1, R28.1, R38.1, R48.1, R49.1, R59.1, R63.2, R64.2, R66.1, R67.2, R75.2, R104.1, R105.1, SW1.1, U4.19 (DIG_VDD), U17.20 (VCCDIG), U18.18 (OVDD), U19.10 (VDDOB), U19.11 (VDDOA), U19.14 (VDDOD), U19.18 (VDDOC), U19.20 (VDD), U20.8 (VCC), U23.5 (VDDIO), U23.16 (USB0_VDDA3V3_DRIVER), U23.17 (USB0_VDDA3V3), U23.25 (VDDREG), U23.36 (VDDIO), U23.41 (VDDIO), U23.59 (VDDREG), U23.71 (VDDIO), U23.77 (VDDIO), U23.94 (VDDREG), U23.107 (VDDIO), U23.111 (VDDIO), U23.131 (VDDREG), U23.136 (ADC0_7/ADC1_7), U23.137 (VDDA), U23.141 (VDDIO), U24.5 (VAUX), U24.38 (VCCIO1), U24.51 (VCCIO1), U24.88 (VCCIO2), U24.98 (VCCIO2)
XCVR_EN: R41.2, U17.25 (ENABLE), U23.11 (P4_6)
